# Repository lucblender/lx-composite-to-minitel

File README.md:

# lx-composite-to-minitel

KiCad project of a Minitel mod to add composite video input.
Projet KiCad d'une modification de Minitel pour ajouter une entrée vidéo composite.

## Pictures

## En

### Description

*Français en dessous*

The goal of this project is to be able to enter a French Minitel with composite video. This project takes back the work from cfp-radio that you can find on their [website]( https://www.cfp-radio.com/realisations/rea48/minitel-01.html).
The cfp-radio project goal was to give audio and video to a Minitel. In my case, I only took the video part. I took back their schematic and made my own PCB all in SMD. All PCB shown in pictures in this repo are manufactured using [PCBWay](https://pcbway.com) services.

PCBWay provides high-quality PCB manufacturing with reliable service and fast turnaround times, making them my first choice for prototyping as seen in this Minitel project. They can also make more complex PCB to fit any of your requirements.

### KiCad project

The KiCad project can be found under the [av-to-minitel](/av-to-minitel/). The BOM has [mouser](https://www.mouser.ch) reference for all each component.

For the PCB, I created a rounded track version to fit a bit the look of the Minitel PCB with the help of the [kicad-round-tracks](https://github.com/mitxela/kicad-round-tracks) plugin. This PCB is the main PCB [av-to-minitel.kicad_pcb](/av-to-minitel/av-to-minitel.kicad_pcb). The original PCB with normal "square" tracks can be found under the [av-to-minitel-angled.kicad_pcb](/av-to-minitel/av-to-minitel-angled.kicad_pcb) file.

### Assembly

The output connector of the PCB is too small to fit the Minitel board (2.54mm pitch versus 5.08mm pitch). In my case, I unsoldered the original Minitel 5.08 pin header and made a custom adapter cable to fit the Minitel board. See the below picture for more detail.

## Fr

### Description

Le but de ce projet est d'ajouter une entrée composite vidéo à un minitel français. Ce projet reprend le travail de cfp-radio qui peut être retrouvé sur leur site [internet]( https://www.cfp-radio.com/realisations/rea48/minitel-01.html).

Le but du projet de cfp-radio est de rajouter de l'audio et de la vidéo à un minitel. Dans mon cas, je n'ai réalisé que la partie vidéo. J'ai repris leur schématique et réalisé mon propre PCB en smd. Tous les PCBs montrés dans ce repo ont été fabriqués à l'aide des services de [PCBWay](https://pcbway.com).

PCBWay propose une fabrication de PCB de haute qualité avec un service fiable et des délais d'exécution rapides, ce qui en fait mon premier choix pour le prototypage comme le montre ce projet lié au Minitel. Ils peuvent également fabriquer des PCBs plus complexes pour répondre à toutes vos exigences.

### Projet KiCad

Le projet KiCad se trouve dans le dossier [av-to-minitel](/av-to-minitel/). La BOM contient des références [mouser](https://www.mouser.ch) pour chaque composant.

Pour le PCB, j'ai utilisé des pistes arrondies pour avoir un style similaire au vieux PCB du Minitel avec l'aide du plugin [kicad-round-tracks](https://github.com/mitxela/kicad-round-tracks). Ce PCB est le PCB principal [av-to-minitel.kicad_pcb](/av-to-minitel/av-to-minitel.kicad_pcb). La version originale avec des pistes "coudées" se trouve dans le fichier [av-to-minitel-angled.kicad_pcb](/av-to-minitel/av-to-minitel-angled.kicad_pcb).

### Assemblage

Le connecteur de sortie du PCB est trop petit pour s'adapter à la carte Minitel (espacement de 2,54 mm contre 5,08 mm). Dans mon cas, j'ai dessoudé le pin header d'origine du Minitel de 5,08mm de pitch et fabriqué un câble adaptateur custom pour s'adapter à la carte Minitel. Voir l'image ci-dessous pour plus de détails.

## Assembly - Assemblage

### Adapter cable - Cable d'adaptation

As said earlier, I took back the 5.08 pitch pin header from the minitel "display card" and soldered some wires + 2.54mm pitch connector to make an easy adapter to the board.

### Mouted - Monté

Without the main Minitel "display card" there is enough room to let the new composite adapter card "float" in that new free space.

## Schematic

## License

This project is under [CC BY-SA 4.0](https://creativecommons.org/licenses/by-sa/4.0/) license.

You are free to:

- Share — copy and redistribute the material in any medium or format for any purpose, even commercially.
- Adapt — remix, transform, and build upon the material for any purpose, even commercially.
The licensor cannot revoke these freedoms as long as you follow the license terms.

## Video Demo

Demo with a raspberry pi running [Auto Waaave](https://andreijaycreativecoding.com/AUTO-WAAAVE-MANUAL) by Andrei_Jay.

<https://github.com/user-attachments/assets/5a00ba67-d3fa-4769-bc9c-a68b00cb2784>

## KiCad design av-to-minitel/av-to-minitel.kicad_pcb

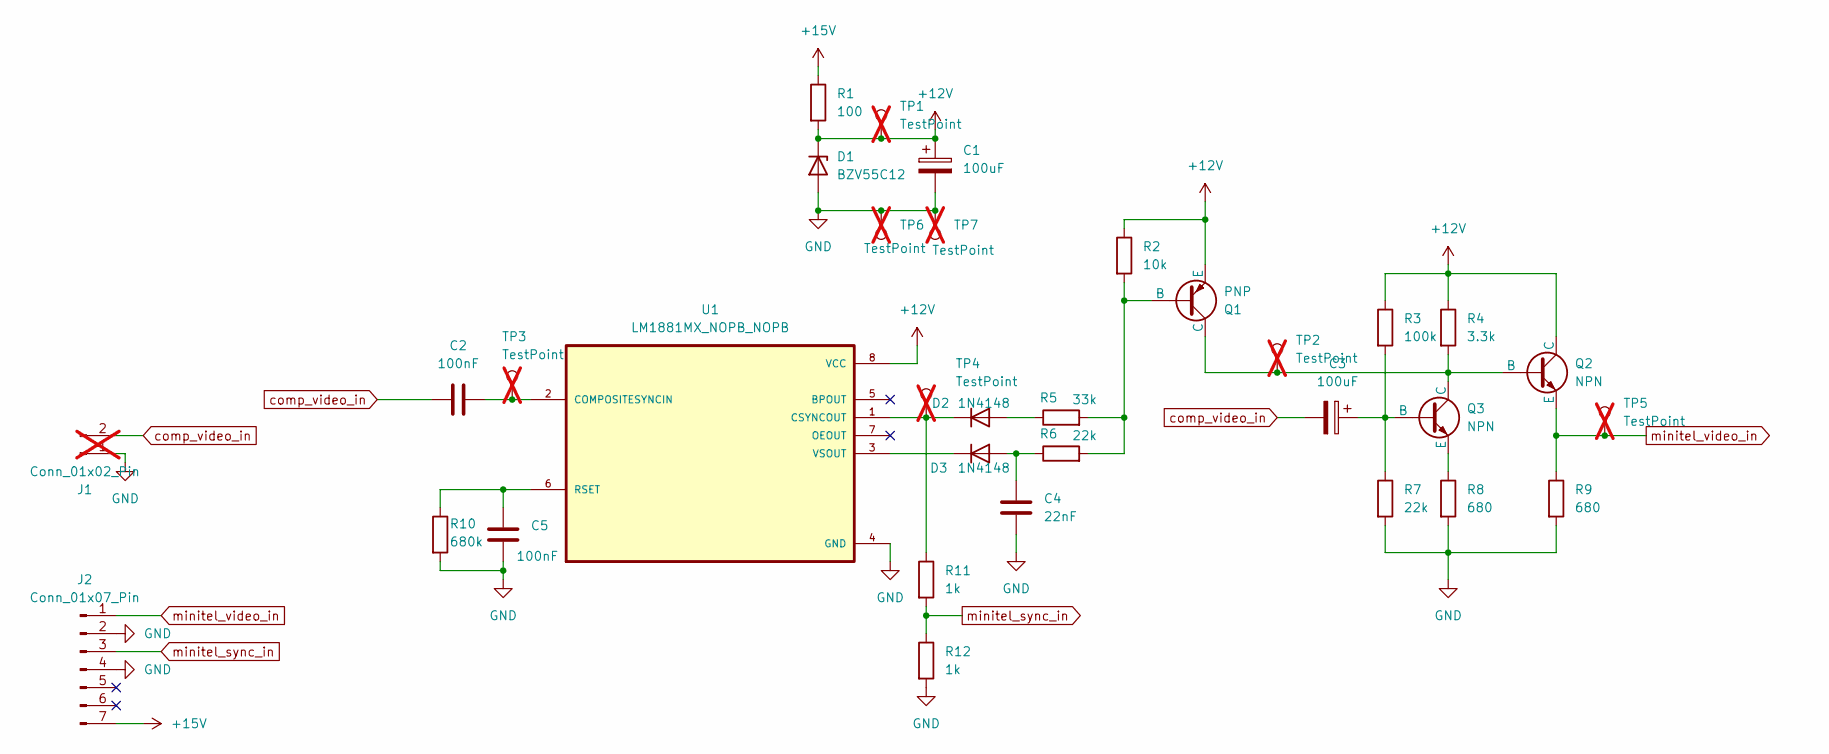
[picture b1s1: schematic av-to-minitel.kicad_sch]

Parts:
C1, C3: 100uF; CP_Elec_5x5.8; Mouser reference 667-EEE-FN1C101UR
C2, C5: 100nF; C_0603_1608Metric; Mouser reference 710-885012206071R
C4: 22nF; C_0603_1608Metric; Mouser reference C0603C223K3RACTM
D1: BZV55C12; D_MiniMELF; Mouser reference 771-BZV55-C12-T/R
D2, D3: 1N4148; D_SOD-323F; Mouser reference 637-1N4148WS-AQ
J1: Conn_01x02_Pin; PinHeader_1x02_P2.54mm_Horizontal; not fitted
J2: Conn_01x07_Pin; PinHeader_1x07_P2.54mm_Horizontal; Mouser reference 649-1012937990701BLF
Q1: PNP; SOT-23; Mouser reference 241-MMBT2907AR100001
Q2, Q3: NPN; SOT-23; Mouser reference 522-FMMT619TA
R1: 100; R_0805_2012Metric; Mouser reference RT0805FRE07100RL
R2: 10k; R_0805_2012Metric; Mouser reference CRCW080510K0JNEC
R3: 100k; R_0805_2012Metric; Mouser reference CRGCQ0805J100K
R4: 3.3k; R_0805_2012Metric; Mouser reference CRCW08053K30JNEA
R5: 33k; R_0805_2012Metric; Mouser reference RC0805JR-1333KL
R6, R7: 22k; R_0805_2012Metric; Mouser reference CR0805-FX-2202ELF
R8, R9: 680; R_0805_2012Metric; Mouser reference CRCW0805680RJNEBC
R10: 680k; R_0805_2012Metric; Mouser reference CR0805-FX-6803ELF
R11, R12: 1k; R_0805_2012Metric; Mouser reference RCA08051K00FKEA
TP1, TP2, TP3, TP4, TP5, TP6, TP7: TestPoint; TestPoint_THTPad_D1.0mm_Drill0.5mm; not fitted
U1: LM1881MX_NOPB_NOPB; SOIC127P599X175-8N; Mouser reference 926-LM1881MX/NOPB

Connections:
+12V: C1.1, D1.1 (K), Q1.3 (E), Q2.1 (C), R1.2, R2.1, R3.1, R4.1, TP1.1, U1.8 (VCC)
+15V: J2.7, R1.1
GND: C1.2, C4.1, C5.1, D1.2 (A), J1.1, J2.2, J2.4, R7.2, R8.2, R9.2, R10.2, R12.2, TP6.1, TP7.1, U1.4 (GND)
unnamed: D2.2 (A), R5.1
unnamed: D2.1 (K), R11.1, TP4.1, U1.1 (CSYNCOUT)
unnamed: C4.2, D3.2 (A), R6.1
unnamed: D3.1 (K), U1.3 (VSOUT)
unnamed: Q1.2 (B), R2.2, R5.2, R6.2
unnamed: Q1.1 (C), Q2.2 (B), Q3.1 (C), R4.2, TP2.1
unnamed: C3.1, Q3.2 (B), R3.2, R7.1
unnamed: Q3.3 (E), R8.1
unnamed: C2.2, TP3.1, U1.2 (COMPOSITESYNCIN)
unnamed: C5.2, R10.1, U1.6 (RSET)
comp_video_in: C2.1, C3.2, J1.2
minitel_sync_in: J2.3, R11.2, R12.1
minitel_video_in: J2.1, Q2.3 (E), R9.1, TP5.1

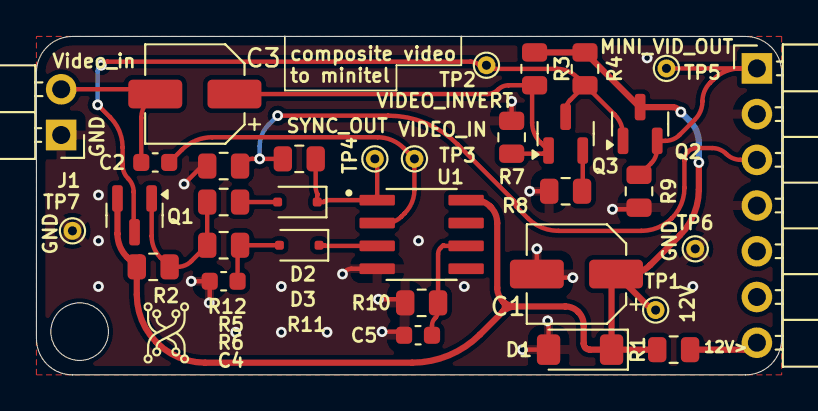
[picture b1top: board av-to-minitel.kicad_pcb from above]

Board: 2 copper layers, 41.4 x 18.8 mm, 33 parts (0 on the bottom side), 16 nets.

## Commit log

2025-01-22 feature: commit source files
2025-01-22 feature: first version of readme
2025-01-22 feature: add pcbway reference and address the connector pitch error
2025-01-22 fix: typos
2025-01-22 fix: mouser links
2025-01-22 feature: add quick description and put pictures first
2025-01-28 fix: fix schematic placement
2025-01-28 feature: add assembly pictures
2025-01-28 fix: add credit for video
2025-02-05 fix: fix readme and put a png of schematic to have white background
2025-02-05 fix: cr in readme
2025-11-24 fix: update to CC BY-SA 4.0 license
